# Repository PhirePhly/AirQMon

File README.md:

# AirQMon
Sensor Hat for the Raspberry Pi

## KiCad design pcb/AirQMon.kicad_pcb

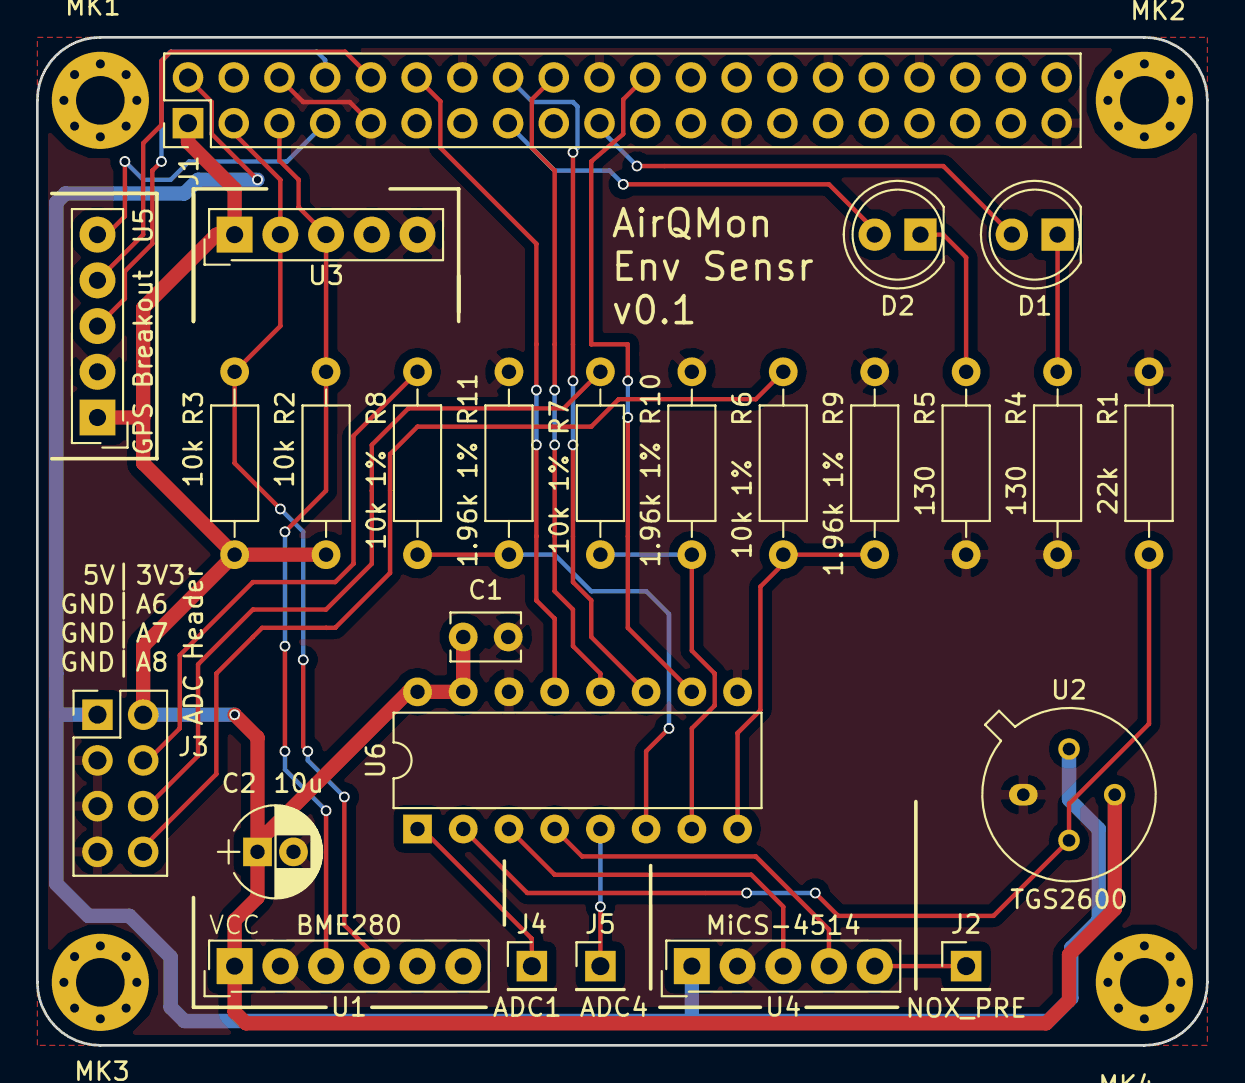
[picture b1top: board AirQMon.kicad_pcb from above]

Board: 2 copper layers, 65.0 x 56.0 mm, 30 parts (0 on the bottom side), 28 nets.

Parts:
C1: 0.1u; C_Disc_D3.8mm_W2.6mm_P2.50mm
C2: 10u; CP_Radial_D5.0mm_P2.00mm
D1, D2: LED; LED_D5.0mm
J1: RaspberryPi Header; Pin_Header_Straight_2x20_Pitch2.54mm
J2: NOX_PRE; Pin_Header_Straight_1x01_Pitch2.54mm
J3: ADC Header; Pin_Header_Straight_2x04_Pitch2.54mm
J4: ADC1; Pin_Header_Straight_1x01_Pitch2.54mm
J5: ADC4; Pin_Header_Straight_1x01_Pitch2.54mm
MK1, MK2, MK3, MK4: Mounting_Hole_PAD; MountingHole_2.7mm_M2.5_Pad_Via
R1: 22k; R_Axial_DIN0207_L6.3mm_D2.5mm_P10.16mm_Horizontal
R2, R3: 10k; R_Axial_DIN0207_L6.3mm_D2.5mm_P10.16mm_Horizontal
R4, R5: 130; R_Axial_DIN0207_L6.3mm_D2.5mm_P10.16mm_Horizontal
R6, R7, R8: 10k 1%; R_Axial_DIN0207_L6.3mm_D2.5mm_P10.16mm_Horizontal
R9, R10, R11: 1.96k 1%; R_Axial_DIN0207_L6.3mm_D2.5mm_P10.16mm_Horizontal
U1: BME280; SL-106-X-XX_1x06
U2: TGS2600; TO-5-4
U3: RTC_hat; SL-105-X-XX_1x05
U4: MiCS-4514; SL-105-X-XX_1x05
U5: GPS Breakout; SL-105-X-XX_1x05
U6: MCP3008; DIP-16_W7.62mm

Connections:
+3V3: C1.1, C2.1, J1.1, J3.2, R2.2, R3.2, U1.1, U2.3, U3.1, U5.1, U6.15, U6.16
+5V: J1.2, J1.4, J3.1, U2.4, U4.1
ADC6: R8.1, R11.2, U6.6
ADC7: R7.1, R10.2, U6.7
ADC8: R6.1, R9.2, U6.8
CS_ADC: J1.22, U6.10
GND: C1.2, C2.2, J1.6, J1.9, J1.14, J1.20, J1.25, J1.30, J1.34, J1.39, J3.3, J3.5, J3.7, R1.2, R4.2, R5.2, R9.1, R10.1, R11.1, U1.2, U2.1, U3.5, U4.2, U5.2, U6.9, U6.14
MISO: J1.18, U6.12
MOSI: J1.16, U6.11
NOX: U4.4, U6.4
unnamed: D1.1, R4.1
unnamed: D1.2, J1.19
unnamed: D2.1, R5.1
unnamed: D2.2, J1.15
unnamed: J2.1, U4.5
unnamed: J3.4, R8.2
unnamed: J3.6, R7.2
unnamed: J3.8, R6.2
unnamed: J4.1, U6.1
unnamed: J5.1, U6.5
PPS: J1.7, U5.5
RED: U4.3, U6.3
RXD: J1.10, U5.4
SCL: J1.5, R2.1, U1.3, U3.3
SCLK: J1.12, U6.13
SDA: J1.3, R3.1, U1.4, U3.2
TGS_OUT: R1.1, U2.2, U6.2
TXD: J1.8, U5.3

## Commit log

2017-09-05 Initial schematic with just headers and ADC
2017-09-05 Added BME280, TGS2600, GPS, and RTC modules
2017-10-02 Added CO/NOX sensor to schematic
2017-10-05 Added I2C pullup, Refdes, and header NCs
2017-12-18 Rough board outline and component placement
2018-02-21 Silk screen cleanup
